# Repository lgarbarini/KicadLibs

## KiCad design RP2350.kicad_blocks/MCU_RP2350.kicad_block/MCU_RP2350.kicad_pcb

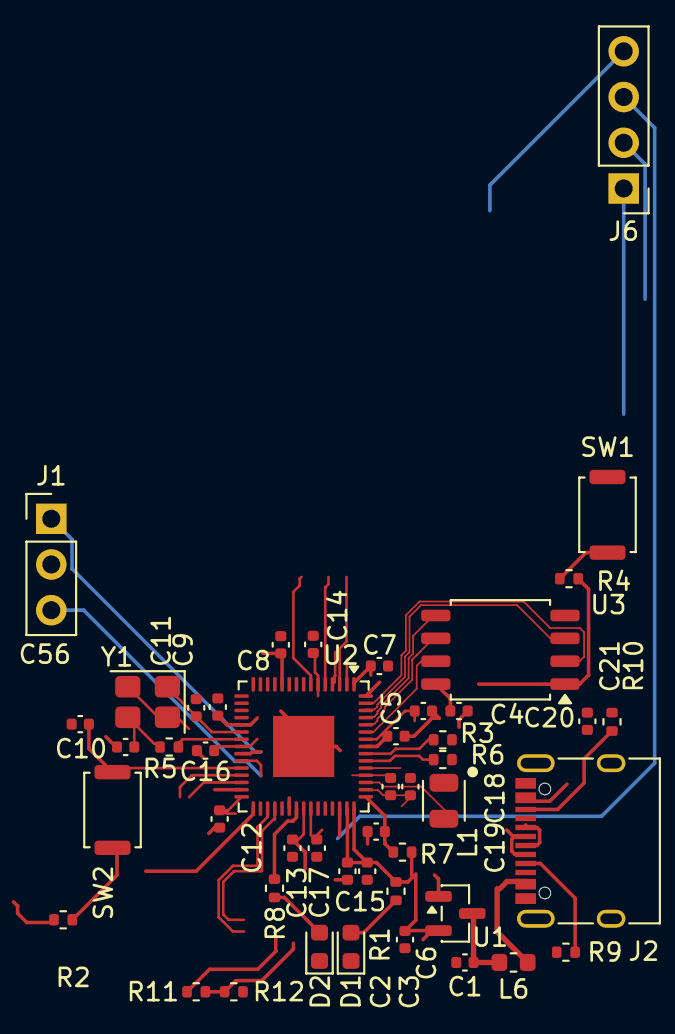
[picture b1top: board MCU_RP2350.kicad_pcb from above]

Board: 4 copper layers, 47 parts (0 on the bottom side), 32 nets.

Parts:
C1, C6: 10u; C_0402_1005Metric
C2, C3, C4, C5, C7, C8, C11, C12, C13, C14, C16, C20, C56: 100n; C_0402_1005Metric
C9, C10: 15p; C_0402_1005Metric
C15, C17, C18, C19: 4u7; C_0402_1005Metric
C21: 2u2; C_0402_1005Metric
D1, D2: LED; LED_0603_1608Metric
J1: Conn_01x03_Pin; PinHeader_1x03_P2.54mm_Vertical
J2: USB_C_Receptacle; USB_C_Receptacle_XKB_U262-16XN-4BVC11
J6: Conn_01x04_Pin; PinHeader_1x04_P2.54mm_Vertical
L1: AOTA-B201610S3R3-101-T
L6: BLM18EG471SN1D; L_0603_1608Metric
R1, R8: 100; R_0402_1005Metric
R2, R4, R5: 1k; R_0402_1005Metric
R3, R6: 27; R_0402_1005Metric
R7: 33; R_0402_1005Metric
R9, R10: 5k1; R_0402_1005Metric
R11: 51k; R_0402_1005Metric
R12: 100k; R_0402_1005Metric
SW1, SW2: SW_Push; SW_Push_SPST_NO_Alps_SKRK
U1: MCP1703AT-3302E/CB; SOT-23
U2: RP2350A; QFN-60-1EP_7x7mm_P0.4mm_EP3.4x3.4mm
U3: W25Q128JVS; SOIC-8_5.3x5.3mm_P1.27mm
Y1: ABM8-272-T3; Crystal_SMD_Abracon_ABM8G-4Pin_3.2x2.5mm

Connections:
+1V1: C14.1, C16.1, C17.1, C19.1, L1.1, U2.6 (DVDD), U2.23 (DVDD), U2.39 (DVDD), U2.50 (VREG_FB)
+3V3: C2.1, C3.1, C4.1, C5.1, C6.1, C7.1, C8.1, C11.1, C12.1, C13.1, C18.1, C20.1, J6.2, R1.1, R7.1, U1.2 (VO), U2.1 (IOVDD), U2.11 (IOVDD), U2.20 (IOVDD), U2.30 (IOVDD), U2.38 (IOVDD), U2.44 (ADC_AVDD), U2.45 (IOVDD), U2.49 (VREG_VIN), U2.53 (USB_OTP_VDD), U2.54 (QSPI_IOVDD), U3.8 (VCC)
+5V: C21.1, J2.A4 (VBUS), J2.A9 (VBUS), J2.B4 (VBUS), J2.B9 (VBUS), J6.1, L6.2, R11.2
/AIO: J6.3, U2.43 (GPIO29/ADC3)
/GPIO24: R11.1, R12.2, U2.36 (GPIO24)
/QSPI_CS: R4.1, U2.60 (~QSPI_SS), U3.1 (~CS)
/QSPI_SCLK: U2.56 (QSPI_SCLK), U3.6 (CLK)
/QSPI_SD0: U2.57 (QSPI_SD0), U3.5 (DI/IO_{0})
/QSPI_SD1: U2.59 (QSPI_SD1), U3.2 (DO/IO_{1})
/QSPI_SD2: U2.58 (QSPI_SD2), U3.3 (~WP/IO_{2})
/QSPI_SD3: U2.55 (QSPI_SD3), U3.7 (~HOLD/~RESET/IO_{3})
/RUN_RC: C56.1, SW2.2, U2.26 (RUN)
/USBC-D+: J2.A6 (D+), J2.B6 (D+), R3.1
/USBC-D-: J2.A7 (D-), J2.B7 (D-), R6.1
GND: C1.2, C2.2, C3.2, C4.2, C5.2, C6.2, C7.2, C8.2, C9.1, C10.1, C11.2, C12.2, C13.2, C14.2, C15.2, C16.2, C17.2, C18.2, C19.2, C20.2, C21.2, C56.2, D1.1 (K), D2.1 (K), J1.2, J2.A1 (GND), J2.A12 (GND), J2.B1 (GND), J2.B12 (GND), J2.S1 (SHIELD), J6.4, R2.2, R9.2, R10.2, R12.1, SW1.1, U1.1 (GND), U2.47 (VREG_PGND), U2.61 (GND), U3.4 (GND), Y1.2 (G), Y1.4 (G)
unnamed: C10.2, R5.2, Y1.3
unnamed: D1.2 (A), R1.2
unnamed: D2.2 (A), R8.1
unnamed: J1.1, U2.24 (SWCLK)
unnamed: J1.3, U2.25 (SWDIO)
unnamed: J2.A5 (CC1), R9.1
unnamed: J2.B5 (CC2), R10.1
unnamed: R2.1, SW2.1
unnamed: R4.2, SW1.2
unnamed: C1.1, L6.1, U1.3 (VI)
unnamed: R8.2, U2.37 (GPIO25)
unnamed: R6.2, U2.51 (USB_DM)
unnamed: R3.2, U2.52 (USB_DP)
unnamed: C15.1, R7.2, U2.46 (VREG_AVDD)
unnamed: L1.2, U2.48 (VREG_LX)
unnamed: C9.2, U2.21 (XIN), Y1.1
unnamed: R5.1, U2.22 (XOUT)
